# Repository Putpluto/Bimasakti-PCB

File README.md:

Collections of Printed Circuit Board for Bimasakti Racing Team UGM

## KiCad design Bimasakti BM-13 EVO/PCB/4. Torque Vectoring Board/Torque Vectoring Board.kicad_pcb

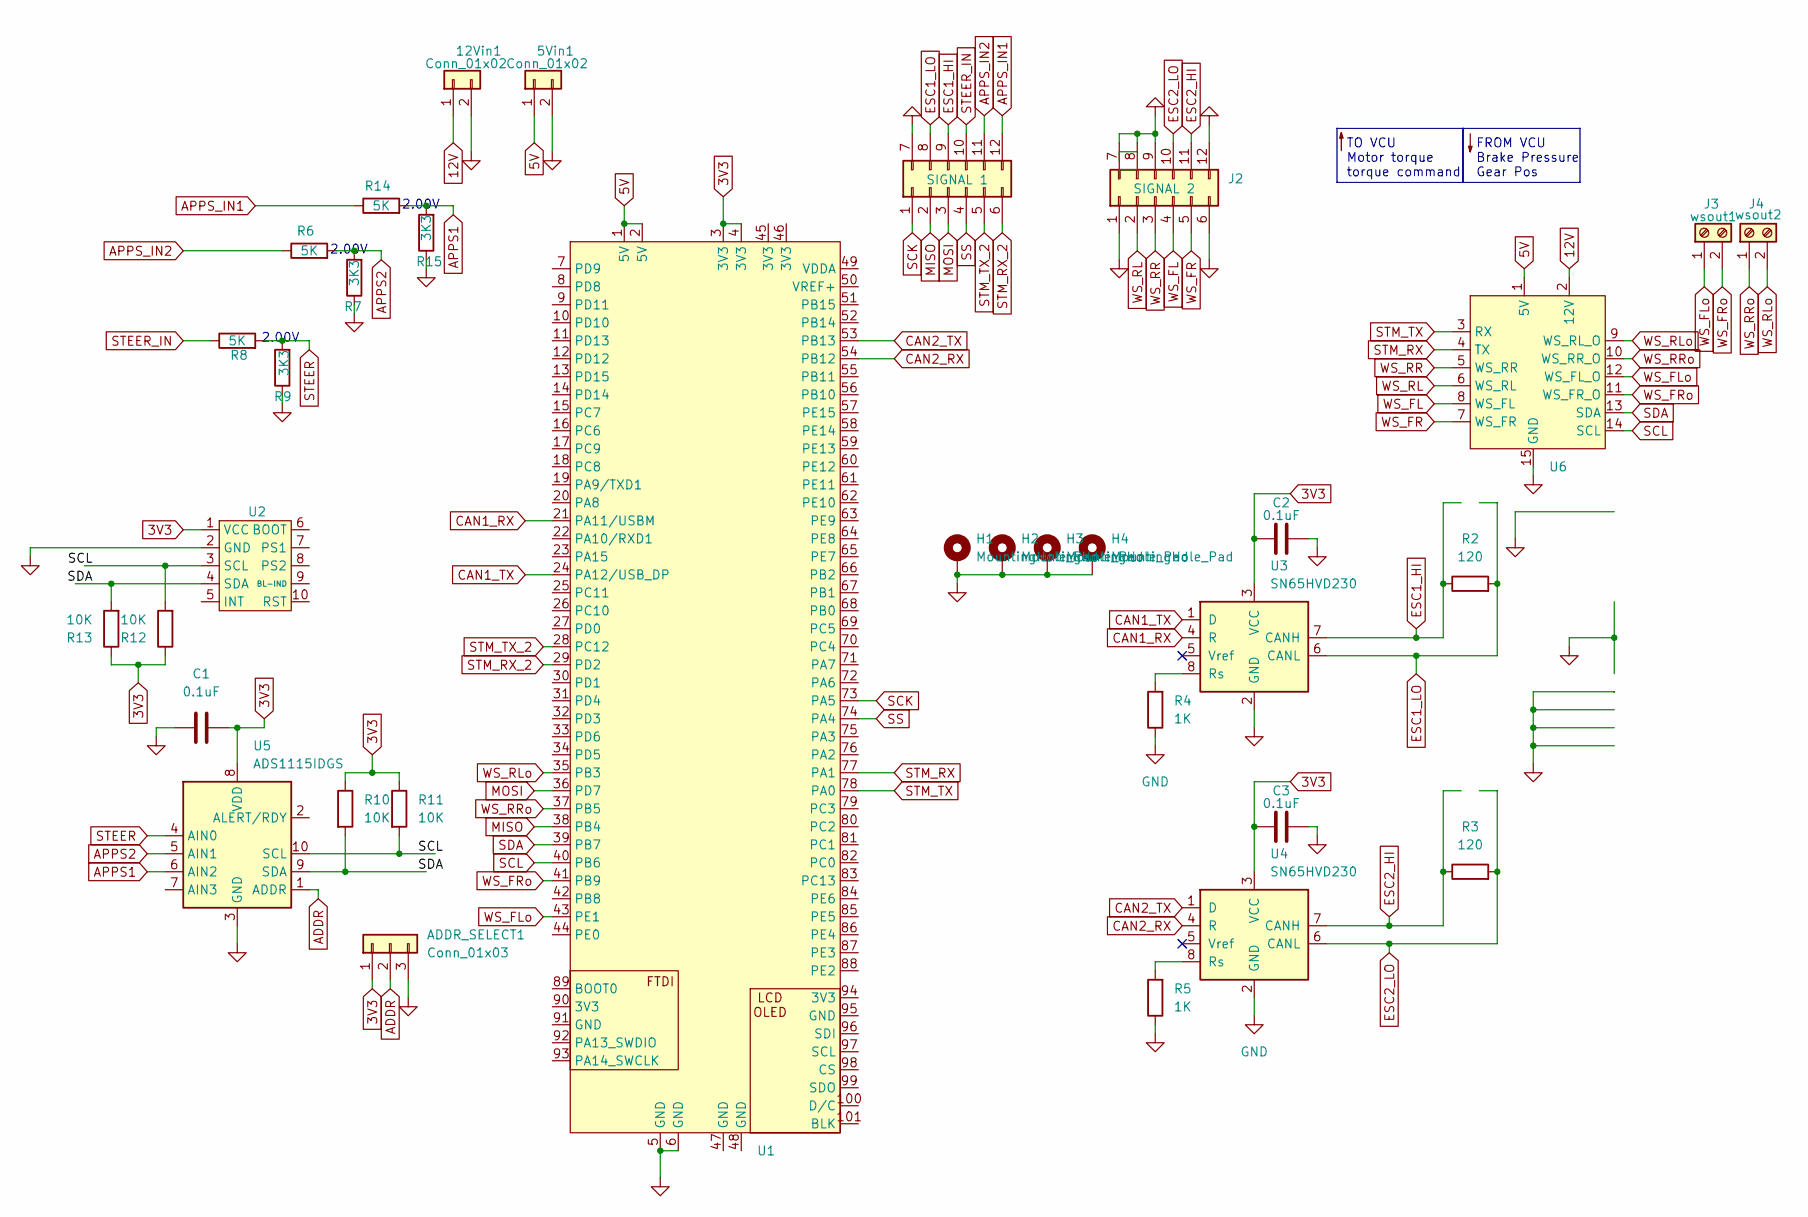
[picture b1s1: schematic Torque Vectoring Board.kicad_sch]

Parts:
5Vin1, 12Vin1: Conn_01x02; Molex_Nano-Fit_105309-xx02_1x02_P2.50mm_Vertical
ADDR_SELECT1: Conn_01x03; PinHeader_1x03_P2.54mm_Vertical
C1, C2, C3: 0.1uF; C_0603_1608Metric
H1, H2, H3, H4: MountingHole_Pad; MountingHole_3.2mm_M3_ISO7380_Pad_TopBottom
J1: SIGNAL 1; Molex_Nano-Fit_105310-xx12_2x06_P2.50mm_Vertical
J2: SIGNAL 2; Molex_Nano-Fit_105310-xx12_2x06_P2.50mm_Vertical
J3: wsout1; Molex_Nano-Fit_105309-xx02_1x02_P2.50mm_Vertical
J4: wsout2; Molex_Nano-Fit_105309-xx02_1x02_P2.50mm_Vertical
R2, R3: 120; R_0603_1608Metric
R4, R5: 1K; R_0603_1608Metric
R6, R8, R14: 5K; R_0603_1608Metric
R7, R9, R15: 3K3; R_0603_1608Metric
R10, R11, R12, R13: 10K; R_0603_1608Metric
U1: STM32H7XX
U2: 0_BNO055
U3, U4: SN65HVD230; SOIC-8_3.9x4.9mm_P1.27mm
U5: ADS1115IDGS; TSSOP-10_3x3mm_P0.5mm
U6: Untitled

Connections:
3V3: ADDR_SELECT1.1, C1.2, C2.1, C3.1, R10.1, R11.1, R12.1, R13.1, U1.3 (3V3), U1.4 (3V3), U2.1 (VCC), U3.3 (VCC), U4.3 (VCC), U5.8 (VDD)
5V: 5Vin1.1, U1.1 (5V), U1.2 (5V), U6.1 (5V)
12V: 12Vin1.1, U6.2 (12V)
ADDR: ADDR_SELECT1.2, U5.1 (ADDR)
APPS1: R14.2, R15.2, U5.6 (AIN2)
APPS2: R6.2, R7.2, U5.5 (AIN1)
APPS_IN1: J1.12, R14.1
APPS_IN2: J1.11, R6.1
CAN1_RX: U1.21 (PA11/USBM), U3.4 (R)
CAN1_TX: U1.24 (PA12/USB_DP), U3.1 (D)
CAN2_RX: U1.54 (PB12), U4.4 (R)
CAN2_TX: U1.53 (PB13), U4.1 (D)
ESC1_HI: J1.9, R2.1, U3.7 (CANH)
ESC1_LO: J1.8, R2.2, U3.6 (CANL)
ESC2_HI: J2.11, R3.1, U4.7 (CANH)
ESC2_LO: J2.10, R3.2, U4.6 (CANL)
GND: 5Vin1.2, 12Vin1.2, ADDR_SELECT1.3, C1.1, C2.2, C3.2, H1.1, H2.1, H3.1, H4.1, J1.7, J2.1, J2.6, J2.7, J2.8, J2.9, J2.12, R4.1, R5.1, R7.1, R9.1, R15.1, U1.5 (GND), U1.6 (GND), U2.2 (GND), U3.2 (GND), U4.2 (GND), U5.3 (GND), U6.15 (GND)
MISO: J1.2, U1.38 (PB4)
MOSI: J1.3, U1.36 (PD7)
unnamed: R4.2, U3.8 (Rs)
unnamed: R5.2, U4.8 (Rs)
SCK: J1.1, U1.73 (PA5)
SCL: R11.2, R12.2, U1.40 (PB6), U2.3 (SCL), U5.10 (SCL), U6.14 (SCL)
SDA: R10.2, R13.2, U1.39 (PB7), U2.4 (SDA), U5.9 (SDA), U6.13 (SDA)
SS: J1.4, U1.74 (PA4)
STEER: R8.2, R9.2, U5.4 (AIN0)
STEER_IN: J1.10, R8.1
STM_RX: U1.77 (PA1), U6.4 (TX)
STM_RX_2: J1.6, U1.29 (PD2)
STM_TX: U1.78 (PA0), U6.3 (RX)
STM_TX_2: J1.5, U1.28 (PC12)
WS_FL: J2.4, U6.8 (WS_FL)
WS_FLo: J3.1, U1.43 (PE1), U6.12 (WS_FL_O)
WS_FR: J2.5, U6.7 (WS_FR)
WS_FRo: J3.2, U1.41 (PB9), U6.11 (WS_FR_O)
WS_RL: J2.2, U6.6 (WS_RL)
WS_RLo: J4.2, U1.35 (PB3), U6.9 (WS_RL_O)
WS_RR: J2.3, U6.5 (WS_RR)
WS_RRo: J4.1, U1.37 (PB5), U6.10 (WS_RR_O)

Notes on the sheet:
FROM VCU Brake Pressure Gear Pos
2.00V
TO VCU Motor torque torque command

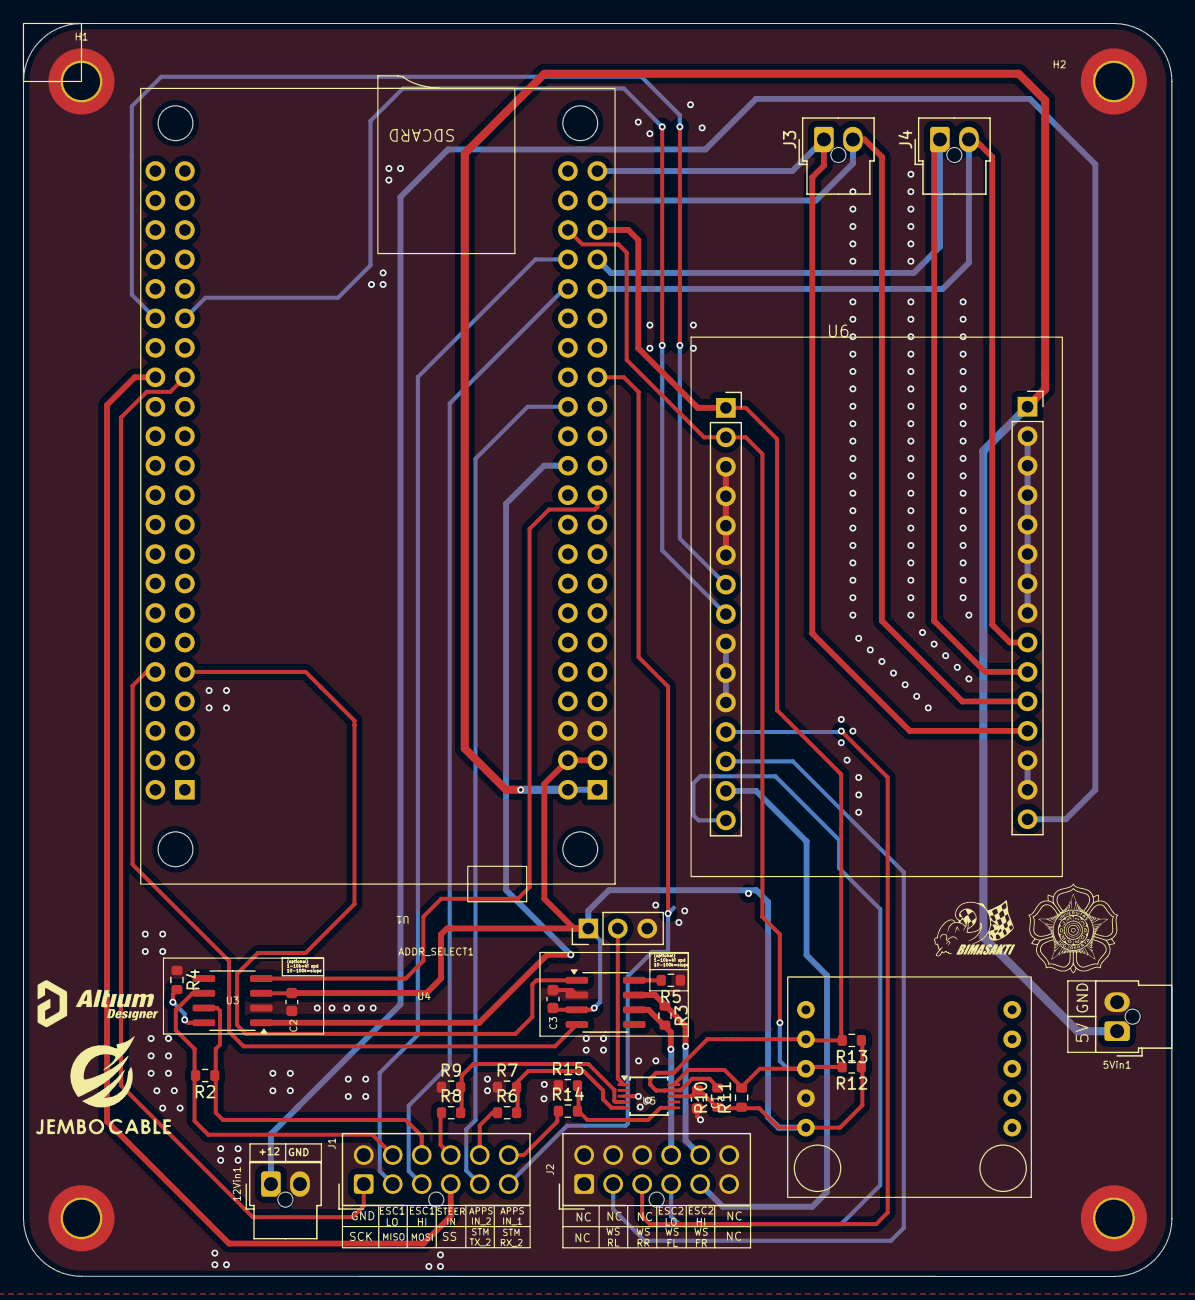
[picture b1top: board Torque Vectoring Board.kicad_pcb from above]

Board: 2 copper layers, 99.0 x 108.0 mm, 35 parts (0 on the bottom side), 39 nets.

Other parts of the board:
a: LOGO; 11jembo_tulisan_12x8.7

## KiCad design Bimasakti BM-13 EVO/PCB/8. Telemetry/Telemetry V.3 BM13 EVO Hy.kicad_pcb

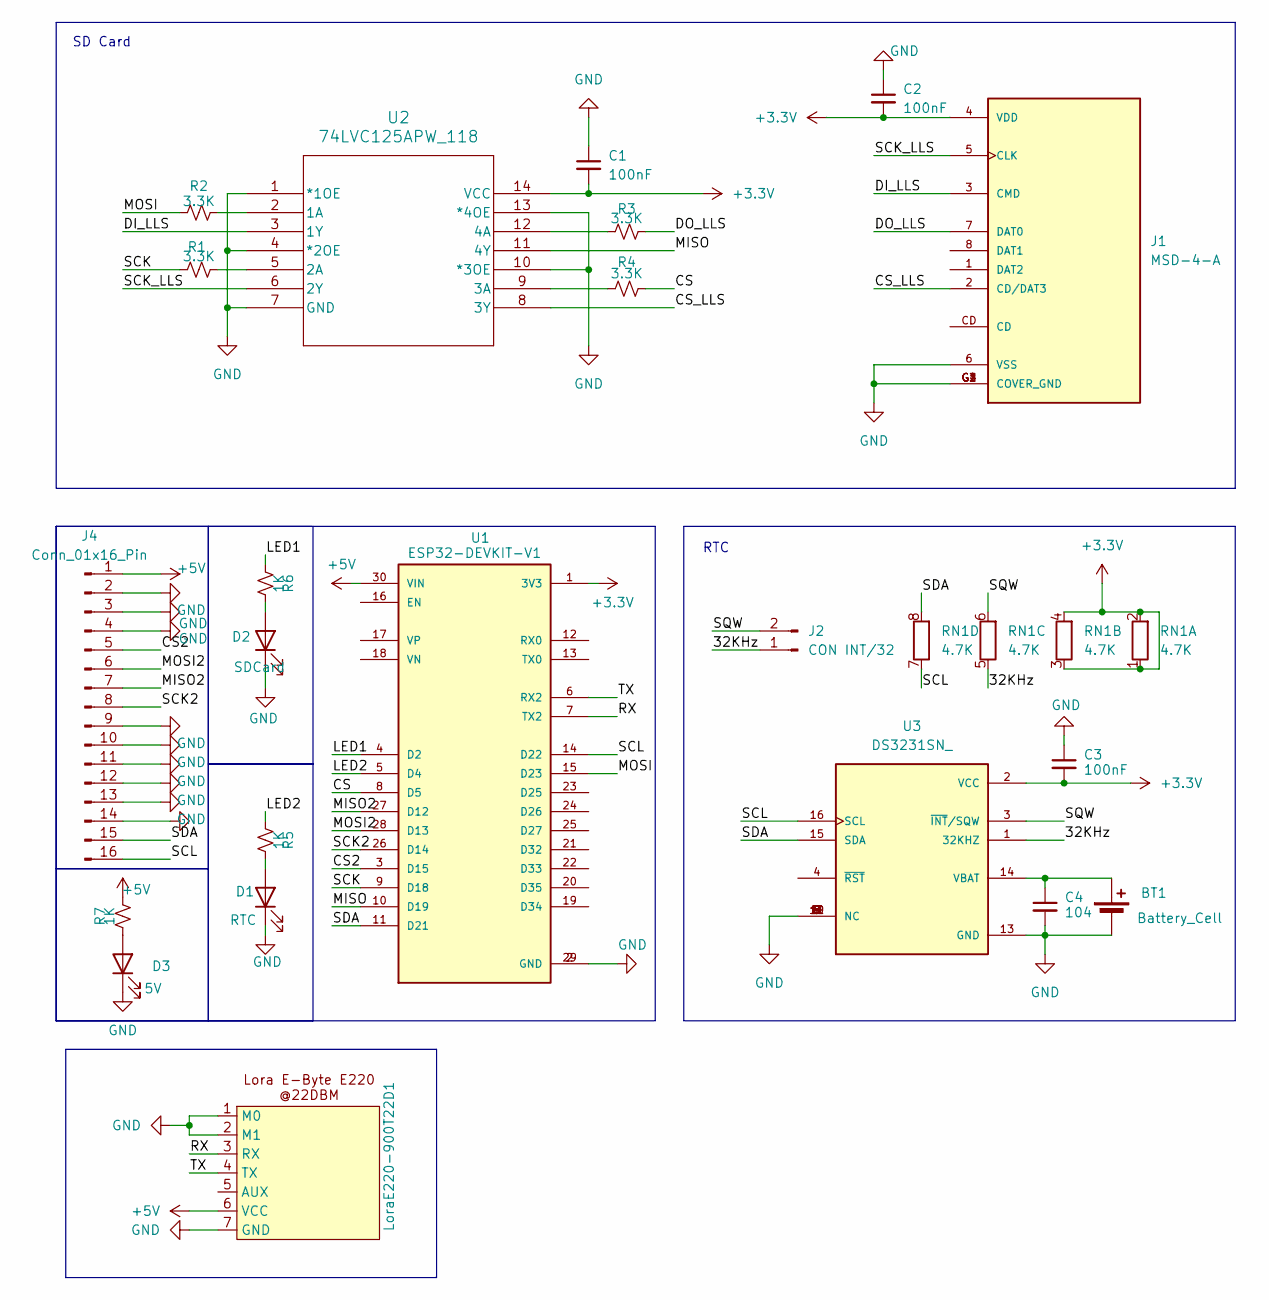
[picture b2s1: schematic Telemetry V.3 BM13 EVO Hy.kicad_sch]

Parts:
BT1: Battery_Cell; BatteryHolder_MYOUNG_BS-07-A1BJ001_CR2032
C1, C2, C3: 100nF; C_0603_1608Metric_Pad1.08x0.95mm_HandSolder
C4: 104; C_0603_1608Metric_Pad1.08x0.95mm_HandSolder
D1: RTC; LED_0603_1608Metric_Pad1.05x0.95mm_HandSolder
D2: SDCard; LED_0603_1608Metric_Pad1.05x0.95mm_HandSolder
D3: 5V; LED_0603_1608Metric_Pad1.05x0.95mm_HandSolder
J1: MSD-4-A; CUI_MSD-4-A; PARTREV 1.0
J2: CON INT/32; PinHeader_1x02_P2.54mm_Vertical
J4: Conn_01x16_Pin; PinHeader_1x16_P2.54mm_Vertical
LoraE220-900T22D1: Lora E220-900T22D
R1, R2, R3, R4: 3.3K; R_0603_1608Metric_Pad0.98x0.95mm_HandSolder
R5, R6, R7: 1K; R_0603_1608Metric_Pad0.98x0.95mm_HandSolder
RN1: 4.7K; R_Array_Convex_4x0603
U1: ESP32-DEVKIT-V1; MODULE_ESP32_DEVKIT_V1; PARTREV N/A
U2: 74LVC125APW_118; TSSOP14_SOT402-1_NEX
U3: DS3231SN_; SOIC127P1032X265-16N; PARTREV 10

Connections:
+3.3V: C1.2, C2.2, C3.2, J1.4 (VDD), RN1.1 (R1.1), RN1.2 (R1.2), RN1.3 (R2.1), RN1.4 (R2.2), U1.1 (3V3), U2.14 (VCC), U3.2 (VCC)
+5V: J4.1, LoraE220-900T22D1.6 (VCC), R7.2, U1.30 (VIN)
/32KHz: J2.1, RN1.5 (R3.1), U3.1 (32KHZ)
/CS: R4.2, U1.8 (D5)
/CS2: J4.5, U1.3 (D15)
/CS_LLS: J1.2 (CD/DAT3), U2.8 (3Y)
/DI_LLS: J1.3 (CMD), U2.3 (1Y)
/DO_LLS: J1.7 (DAT0), R3.2
/LED1: R6.1, U1.4 (D2)
/LED2: R5.1, U1.5 (D4)
/MISO: U1.10 (D19), U2.11 (4Y)
/MISO2: J4.7, U1.27 (D12)
/MOSI: R2.1, U1.15 (D23)
/MOSI2: J4.6, U1.28 (D13)
/RX: LoraE220-900T22D1.3 (RX), U1.7 (TX2)
/SCK: R1.1, U1.9 (D18)
/SCK2: J4.8, U1.26 (D14)
/SCK_LLS: J1.5 (CLK), U2.6 (2Y)
/SCL: J4.16, RN1.7 (R4.1), U1.14 (D22), U3.16 (SCL)
/SDA: J4.15, RN1.8 (R4.2), U1.11 (D21), U3.15 (SDA)
/SQW: J2.2, RN1.6 (R3.2), U3.3 (~INT/SQW)
/TX: LoraE220-900T22D1.4 (TX), U1.6 (RX2)
GND: BT1.2 (-), C1.1, C2.1, C3.1, C4.2, D1.1 (K), D2.1 (K), D3.1 (K), J1.6 (VSS), J1.G1 (COVER_GND), J1.G2 (COVER_GND), J1.G3 (COVER_GND), J1.G4 (COVER_GND), J4.2, J4.3, J4.4, J4.9, J4.10, J4.11, J4.12, J4.13, J4.14, LoraE220-900T22D1.1 (M0), LoraE220-900T22D1.2 (M1), LoraE220-900T22D1.7 (GND), U1.2 (GND), U1.29 (GND), U2.1 (*1OE), U2.4 (*2OE), U2.7 (GND), U2.10 (*3OE), U2.13 (*4OE), U3.5 (NC), U3.6 (NC), U3.7 (NC), U3.8 (NC), U3.9 (NC), U3.10 (NC), U3.11 (NC), U3.12 (NC), U3.13 (GND)
unnamed: BT1.1 (+), C4.1, U3.14 (VBAT)
unnamed: D1.2 (A), R5.2
unnamed: D2.2 (A), R6.2
unnamed: D3.2 (A), R7.1
unnamed: R2.2, U2.2 (1A)
unnamed: R1.2, U2.5 (2A)
unnamed: R4.1, U2.9 (3A)
unnamed: R3.1, U2.12 (4A)

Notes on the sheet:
RTC
SD Card

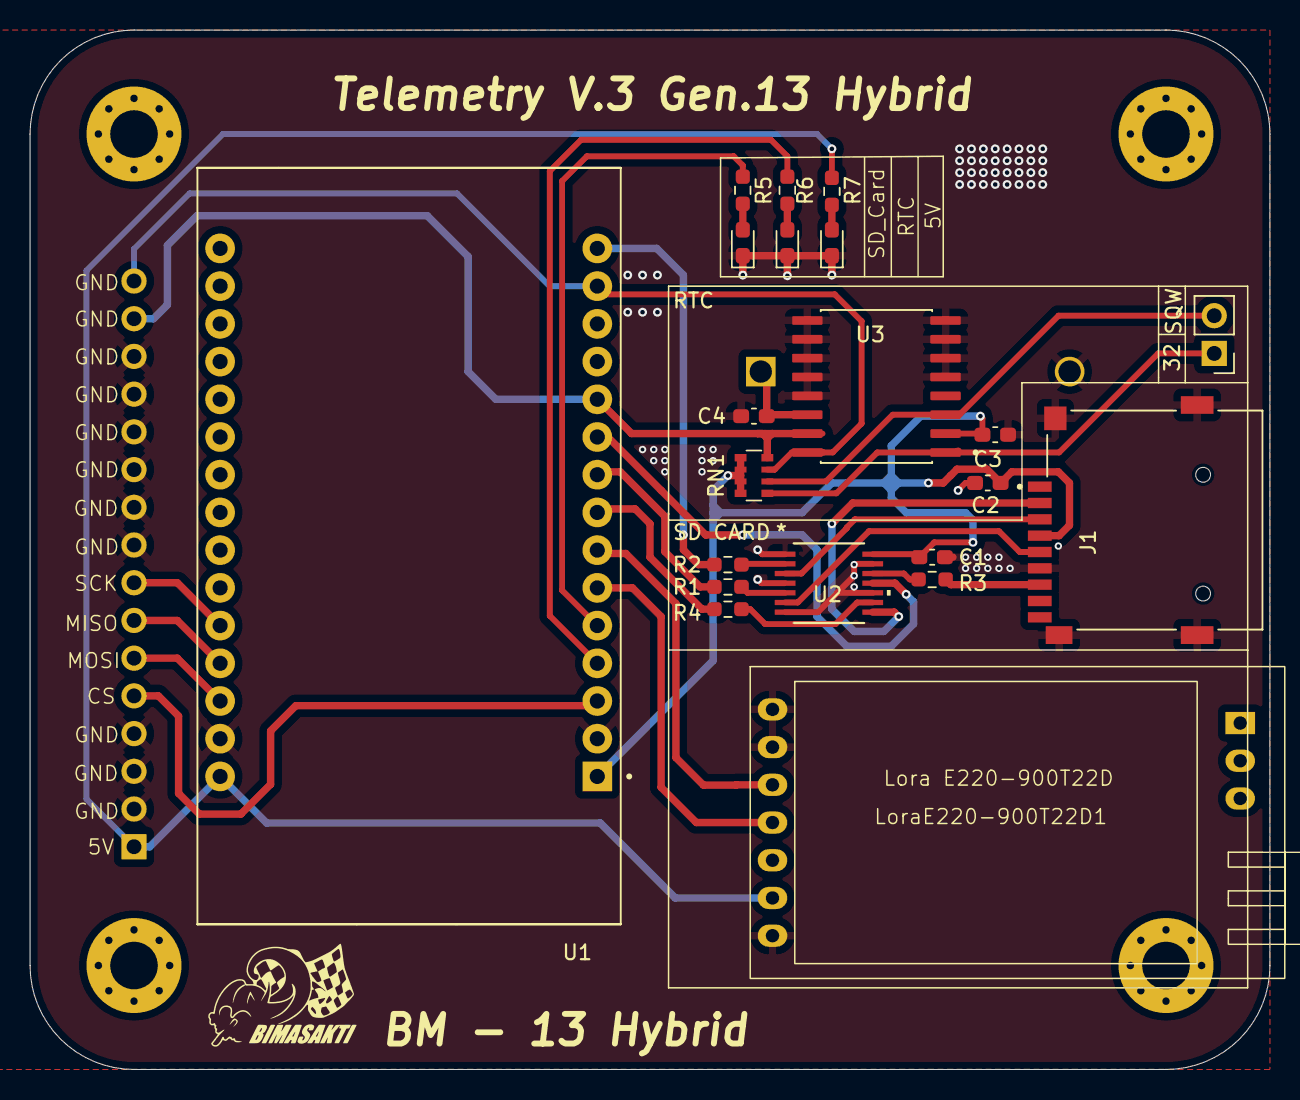
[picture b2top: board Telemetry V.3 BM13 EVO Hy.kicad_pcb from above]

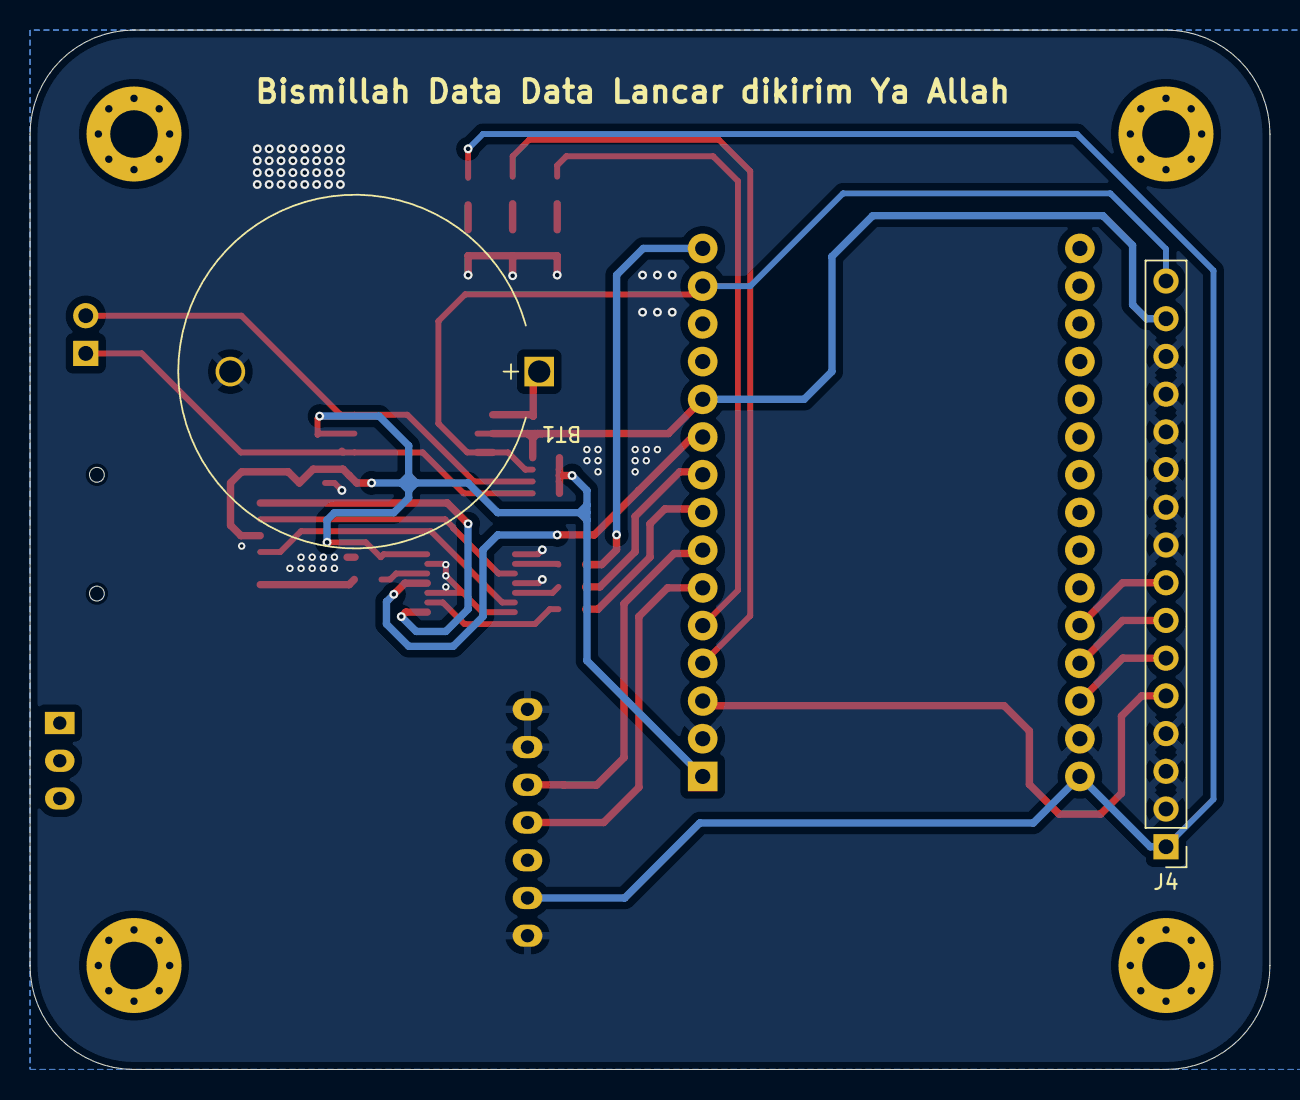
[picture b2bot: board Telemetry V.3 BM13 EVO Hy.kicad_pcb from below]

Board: 2 copper layers, 83.5 x 70.0 mm, 23 parts (2 on the bottom side), 31 nets.

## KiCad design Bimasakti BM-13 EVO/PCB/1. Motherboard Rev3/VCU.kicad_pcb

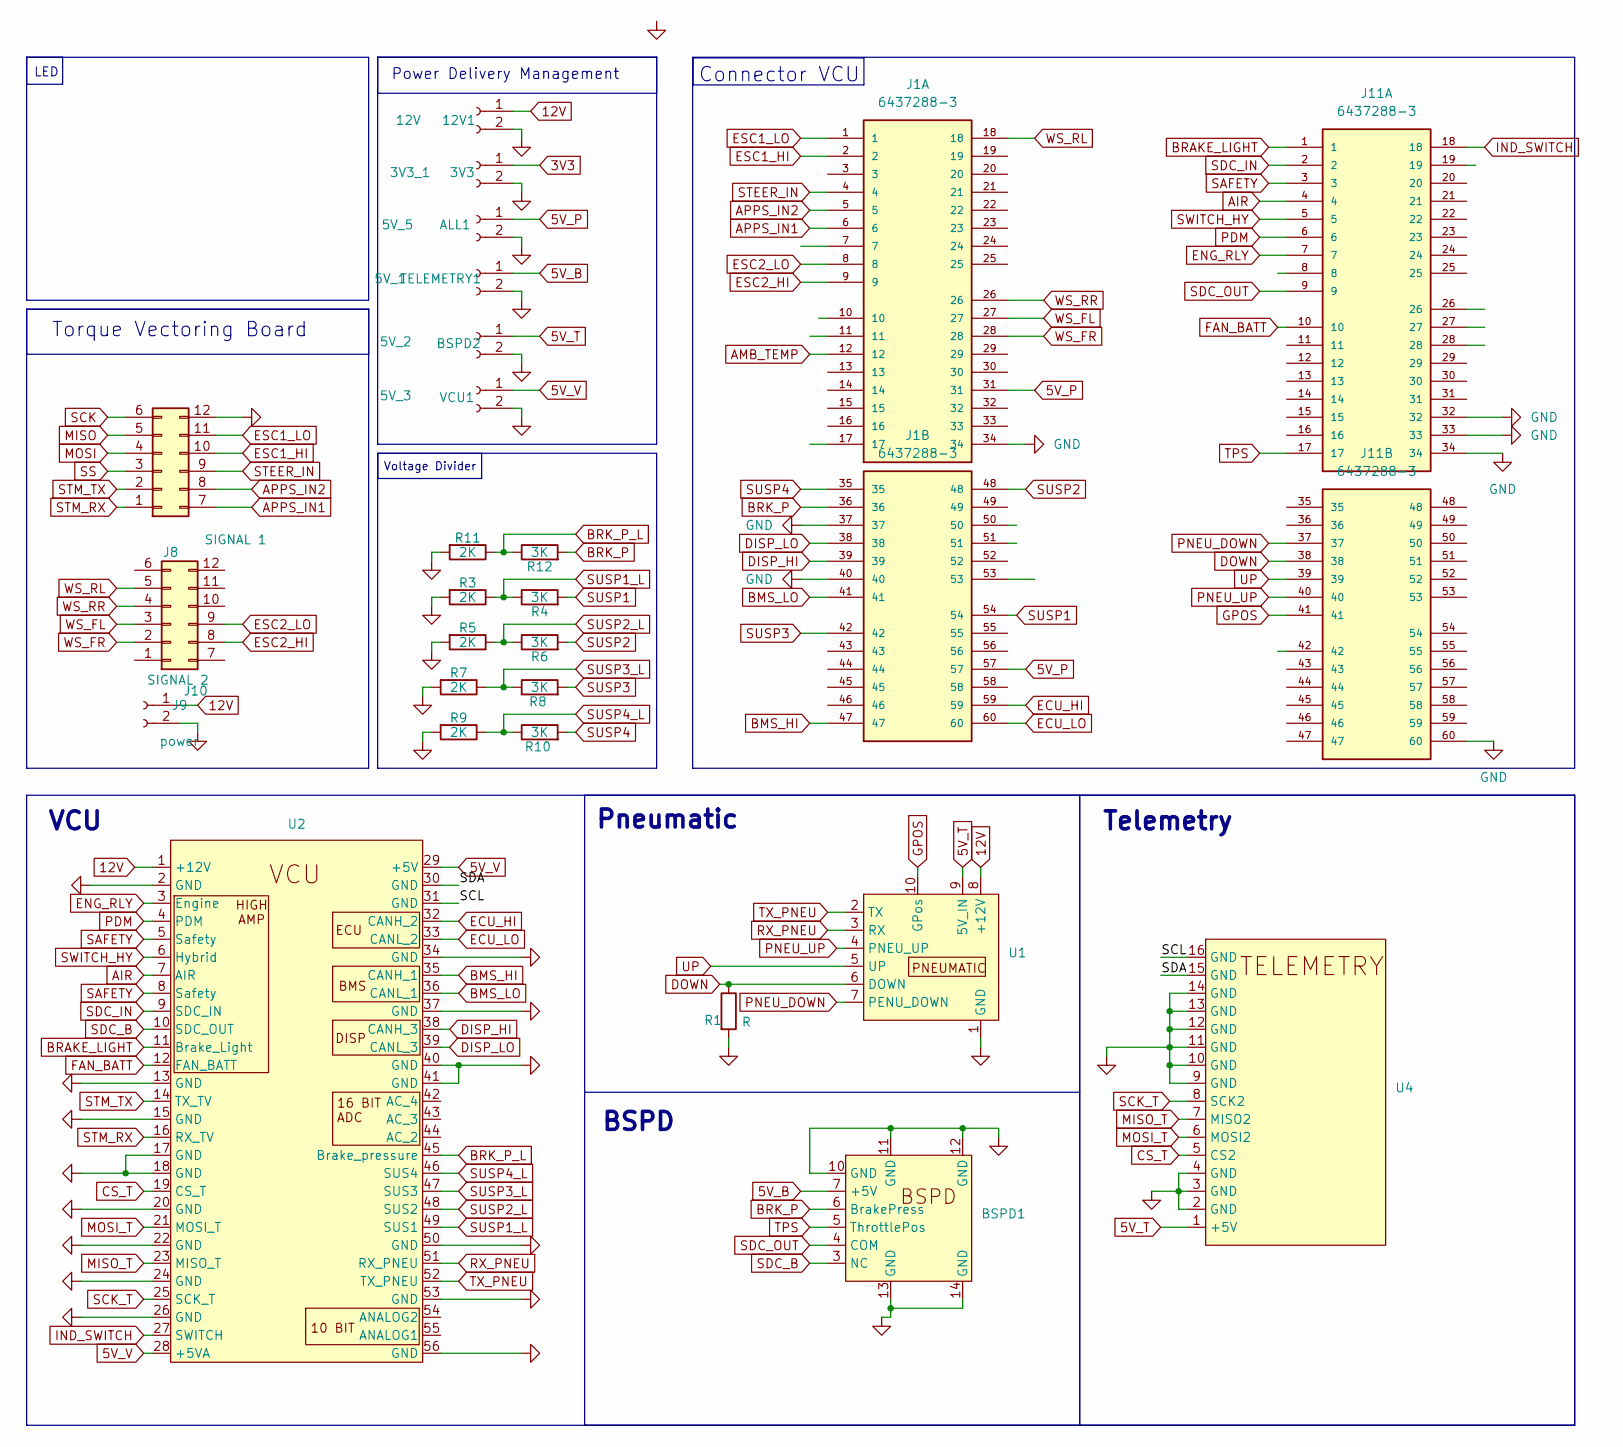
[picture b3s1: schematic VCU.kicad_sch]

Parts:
3V3: 3V3_1; JST_XH_B2B-XH-A_1x02_P2.50mm_Vertical
12V1: 12V; JST_XH_B2B-XH-A_1x02_P2.50mm_Vertical
ALL1: 5V_5; JST_XH_B2B-XH-A_1x02_P2.50mm_Vertical
BSPD1: FootPrintBPSD
BSPD2: 5V_2; JST_XH_B2B-XH-A_1x02_P2.50mm_Vertical
J1, J11: 6437288-3; VCU_CONNECTOR_TE_6437288-3; PARTREV A1
J8: SIGNAL 1; Molex_Nano-Fit_105310-xx12_2x06_P2.50mm_Vertical
J9: SIGNAL 2; Molex_Nano-Fit_105310-xx12_2x06_P2.50mm_Vertical
J10: power; Molex_Nano-Fit_105309-xx02_1x02_P2.50mm_Vertical
R1: R; R_0603_1608Metric_Pad0.98x0.95mm_HandSolder
R3, R5, R7, R9, R11: 2K; R_0603_1608Metric_Pad0.98x0.95mm_HandSolder
R4, R6, R8, R10, R12: 3K; R_0603_1608Metric_Pad0.98x0.95mm_HandSolder
TELEMETRY1: 5V_1; JST_XH_B2B-XH-A_1x02_P2.50mm_Vertical
U1: Fooprint Pneumatic
U2: FootprintVCU
U4: 0_FootprintTelemetry
VCU1: 5V_3; JST_XH_B2B-XH-A_1x02_P2.50mm_Vertical

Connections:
3V3: 3V3.1
5V_B: BSPD1.7 (+5V), TELEMETRY1.1
5V_P: ALL1.1, J1.31, J1.57
5V_T: BSPD2.1, U1.9 (5V_IN), U4.1 (+5V)
5V_V: U2.28 (+5VA), U2.29 (+5V), VCU1.1
12V: 12V1.1, J10.1, U1.8 (+12V), U2.1 (+12V)
/SCL: U2.31 (GND), U4.16 (GND)
/SDA: U2.30 (GND), U4.15 (GND)
AIR: J11.4, U2.7 (AIR)
AMB_TEMP: J1.12
APPS_IN1: J1.6, J8.7
APPS_IN2: J1.5, J8.8
BMS_HI: J1.47, U2.35 (CANH_1)
BMS_LO: J1.41, U2.36 (CANL_1)
BRAKE_LIGHT: J11.1, U2.11 (Brake_Light)
BRK_P: BSPD1.6 (BrakePress), J1.36, R12.2
BRK_P_L: R11.1, R12.1, U2.45 (Brake_pressure)
CS_T: U2.19 (CS_T), U4.5 (CS2)
DISP_HI: J1.39, U2.38 (CANH_3)
DISP_LO: J1.38, U2.39 (CANL_3)
DOWN: J11.38, R1.1, U1.6 (DOWN)
ECU_HI: J1.59, U2.32 (CANH_2)
ECU_LO: J1.60, U2.33 (CANL_2)
ENG_RLY: J11.7, U2.3 (Engine)
ESC1_HI: J1.2, J8.10
ESC1_LO: J1.1, J8.11
ESC2_HI: J1.9, J9.8
ESC2_LO: J1.8, J9.9
FAN_BATT: J11.10, U2.12 (FAN_BATT)
GND: 3V3.2, 12V1.2, ALL1.2, BSPD1.10 (GND), BSPD1.11 (GND), BSPD1.12 (GND), BSPD1.13 (GND), BSPD1.14 (GND), BSPD2.2, J1.34, J1.37, J1.40, J8.12, J10.2, J11.32, J11.33, J11.34, J11.60, R1.2, R3.2, R5.2, R7.2, R9.2, R11.2, TELEMETRY1.2, U1.1 (GND), U2.2 (GND), U2.13 (GND), U2.15 (GND), U2.17 (GND), U2.18 (GND), U2.20 (GND), U2.22 (GND), U2.24 (GND), U2.26 (GND), U2.34 (GND), U2.37 (GND), U2.40 (GND), U2.41 (GND), U2.50 (GND), U2.53 (GND), U2.56 (GND), U4.2 (GND), U4.3 (GND), U4.4 (GND), U4.9 (GND), U4.10 (GND), U4.11 (GND), U4.12 (GND), U4.13 (GND), U4.14 (GND), VCU1.2
GPOS: J11.41, U1.10 (GPos)
IND_SWITCH: J11.18, U2.27 (SWITCH)
MISO: J8.5
MISO_T: U2.23 (MISO_T), U4.7 (MISO2)
MOSI: J8.4
MOSI_T: U2.21 (MOSI_T), U4.6 (MOSI2)
PDM: J11.6, U2.4 (PDM)
PNEU_DOWN: J11.37, U1.7 (PENU_DOWN)
PNEU_UP: J11.40, U1.4 (PNEU_UP)
RX_PNEU: U1.3 (RX), U2.51 (RX_PNEU)
SAFETY: J11.3, U2.5 (Safety), U2.8 (Safety)
SCK: J8.6
SCK_T: U2.25 (SCK_T), U4.8 (SCK2)
SDC_B: BSPD1.3 (NC), U2.10 (SDC_OUT)
SDC_IN: J11.2, U2.9 (SDC_IN)
SDC_OUT: BSPD1.4 (COM), J11.9
SS: J8.3
STEER_IN: J1.4, J8.9
STM_RX: J8.1, U2.16 (RX_TV)
STM_TX: J8.2, U2.14 (TX_TV)
SUSP1: J1.54, R4.2
SUSP1_L: R3.1, R4.1, U2.49 (SUS1)
SUSP2: J1.48, R6.2
SUSP2_L: R5.1, R6.1, U2.48 (SUS2)
SUSP3: J1.42, R8.2
SUSP3_L: R7.1, R8.1, U2.47 (SUS3)
SUSP4: J1.35, R10.2
SUSP4_L: R9.1, R10.1, U2.46 (SUS4)
SWITCH_HY: J11.5, U2.6 (Hybrid)
TPS: BSPD1.5 (ThrottlePos), J11.17
TX_PNEU: U1.2 (TX), U2.52 (TX_PNEU)
UP: J11.39, U1.5 (UP)
WS_FL: J1.27, J9.3
WS_FR: J1.28, J9.2
WS_RL: J1.18, J9.5
WS_RR: J1.26, J9.4

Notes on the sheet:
LED
Connector VCU
VCU
Torque Vectoring Board
Telemetry
Voltage Divider
BSPD
Pneumatic
Power Delivery Management

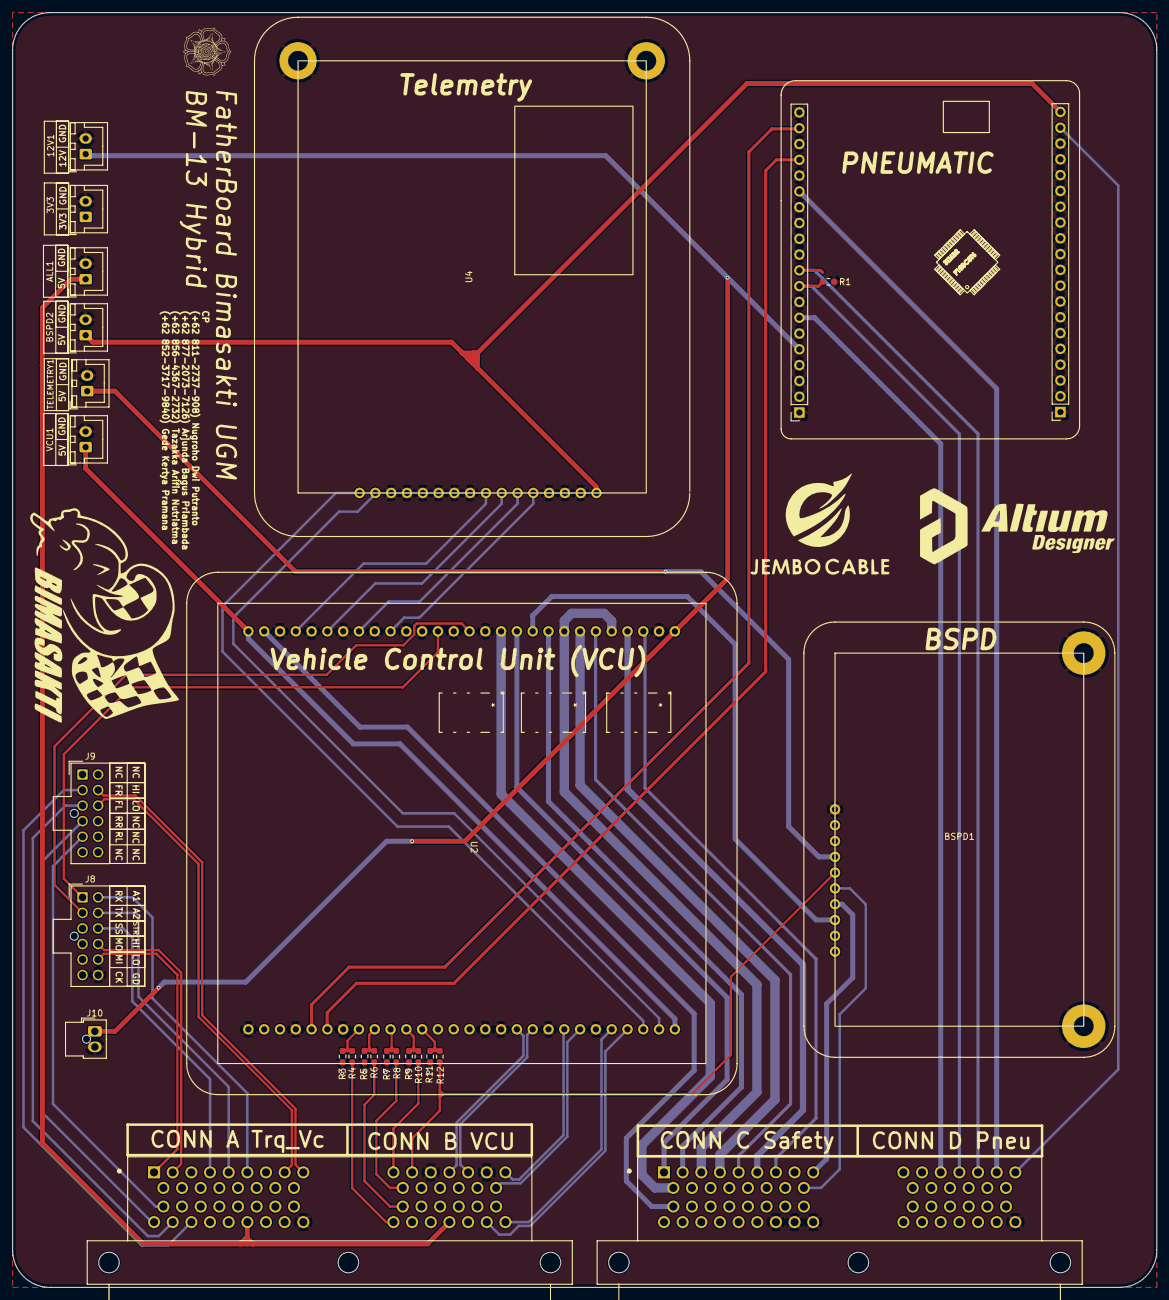
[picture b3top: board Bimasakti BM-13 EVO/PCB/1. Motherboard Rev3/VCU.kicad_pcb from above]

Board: 2 copper layers, 184.0 x 205.0 mm, 26 parts (0 on the bottom side), 60 nets.
